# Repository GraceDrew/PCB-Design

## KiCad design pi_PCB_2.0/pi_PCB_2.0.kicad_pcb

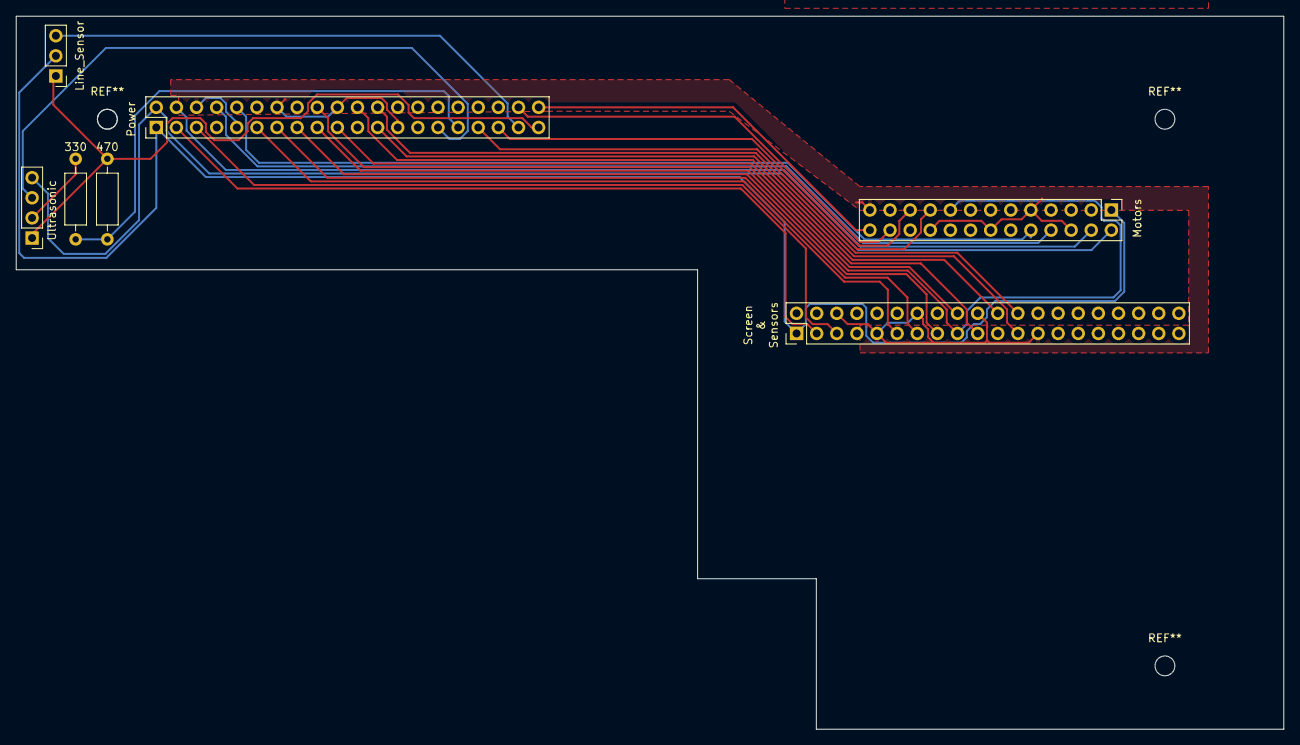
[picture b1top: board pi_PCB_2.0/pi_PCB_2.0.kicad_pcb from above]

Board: 2 copper layers, 160.0 x 90.0 mm, 7 parts (0 on the bottom side), 26 nets.

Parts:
330, 470: R_Small; R_Axial_DIN0207_L6.3mm_D2.5mm_P10.16mm_Horizontal
Line_Sensor: Conn_01x03_Socket; PinHeader_1x03_P2.54mm_Vertical
Motors: Conn_02x13_Odd_Even; PinHeader_2x13_P2.54mm_Vertical
Raspberry_Pi1: Power; PinHeader_2x20_P2.54mm_Vertical
Screen_and_Sensor_Header1: Screen_and_Sensor; PinHeader_2x20_P2.54mm_Vertical
Ultrasonic: Conn_01x04_Socket; PinHeader_1x04_P2.54mm_Vertical

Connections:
unnamed: 470.2, Line_Sensor.1 (Ground), Raspberry_Pi1.39 (GND), Ultrasonic.1 (GND)
unnamed: Line_Sensor.3 (Out), Raspberry_Pi1.37 (GPIO26)
unnamed: Line_Sensor.2 (VCC), Motors.1 (3V3_Power), Raspberry_Pi1.1 (3V3), Screen_and_Sensor_Header1.1 (3.3V_Power)
unnamed: Motors.17 (3V3_Power), Raspberry_Pi1.17 (3V3), Screen_and_Sensor_Header1.17 (3.3V_Power)
unnamed: Motors.4 (5V_Power), Raspberry_Pi1.4 (5V)
unnamed: Motors.19 (GPIO_13), Raspberry_Pi1.33 (PWM1/GPIO13)
unnamed: Motors.8 (GPIO_14), Raspberry_Pi1.8 (GPIO14/TXD)
unnamed: Motors.10 (GPIO_15), Raspberry_Pi1.10 (GPIO15/RXD)
unnamed: Motors.21 (GPIO_19), Raspberry_Pi1.35 (GPIO19/MISO1)
unnamed: Motors.24 (GPIO_20), Raspberry_Pi1.38 (GPIO20/MOSI1)
unnamed: Motors.26 (GPIO_21), Raspberry_Pi1.40 (GPIO21/SCLK1)
unnamed: Motors.6 (Ground), Motors.9 (Ground), Motors.14 (Ground), Motors.20 (Ground), Motors.25 (Ground), Raspberry_Pi1.6 (GND), Raspberry_Pi1.9 (GND), Raspberry_Pi1.14 (GND), Raspberry_Pi1.20 (GND), Raspberry_Pi1.25 (GND), Screen_and_Sensor_Header1.6 (Ground), Screen_and_Sensor_Header1.9 (Ground), Screen_and_Sensor_Header1.14 (Ground), Screen_and_Sensor_Header1.20 (Ground), Screen_and_Sensor_Header1.25 (Ground)
unnamed: Raspberry_Pi1.29 (GCLK1/GPIO5), Ultrasonic.3 (Trig)
unnamed: 330.1, 470.1, Raspberry_Pi1.31 (GCLK2/GPIO6)
unnamed: Raspberry_Pi1.11 (GPIO17), Screen_and_Sensor_Header1.11 (Ext_Reset)
unnamed: Raspberry_Pi1.15 (GPIO22), Screen_and_Sensor_Header1.15 (Touch_rst)
unnamed: Raspberry_Pi1.18 (GPIO24), Screen_and_Sensor_Header1.18 (Busy_out)
unnamed: Raspberry_Pi1.22 (GPIO25), Screen_and_Sensor_Header1.22 (Data_ctrl)
unnamed: Raspberry_Pi1.13 (GPIO27), Screen_and_Sensor_Header1.13 (Touch_iterp)
unnamed: Raspberry_Pi1.19 (MOSI0/GPIO10), Screen_and_Sensor_Header1.19 (SPI_MOSI)
unnamed: Raspberry_Pi1.23 (SCLK0/GPIO11), Screen_and_Sensor_Header1.23 (SPI_SCLK)
unnamed: Raspberry_Pi1.5 (SCL/GPIO3), Screen_and_Sensor_Header1.5 (Touch_Clk)
unnamed: Raspberry_Pi1.3 (SDA/GPIO2), Screen_and_Sensor_Header1.3 (Touch_Data)
unnamed: Raspberry_Pi1.24 (~CE0/GPIO8), Screen_and_Sensor_Header1.24 (SPI_select)
unnamed: 330.2, Ultrasonic.2 (Echo)
unnamed: Motors.2 (5V_Power), Raspberry_Pi1.2 (5V), Ultrasonic.4 (VCC)

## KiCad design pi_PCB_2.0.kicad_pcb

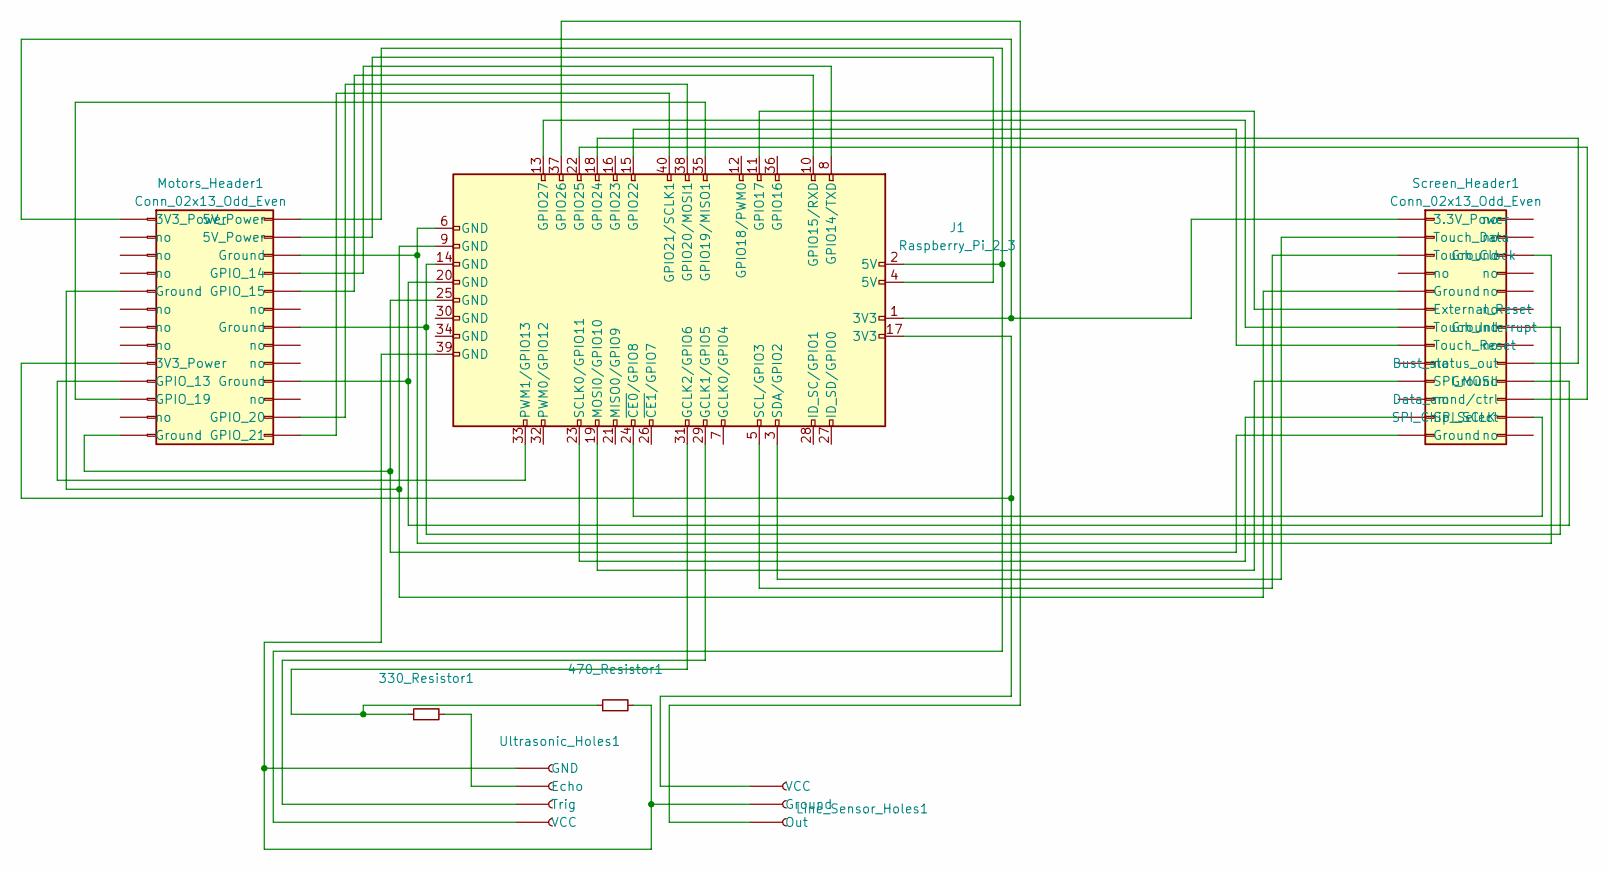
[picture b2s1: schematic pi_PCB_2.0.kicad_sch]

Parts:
330_Resistor1, 470_Resistor1: R_Small; R_Axial_DIN0204_L3.6mm_D1.6mm_P1.90mm_Vertical
J1: Raspberry_Pi_2_3; PinHeader_2x20_P2.54mm_Vertical
Line_Sensor_Holes1: Conn_01x03_Socket; PinHeader_1x03_P2.54mm_Vertical
Motors_Header1: Conn_02x13_Odd_Even; PinHeader_2x13_P2.54mm_Vertical
Screen_Header1: Conn_02x13_Odd_Even; PinHeader_2x13_P2.54mm_Vertical
Ultrasonic_Holes1: Conn_01x04_Socket; PinHeader_1x04_P2.54mm_Vertical

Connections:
unnamed: J1.4 (5V), Motors_Header1.4 (5V_Power)
unnamed: J1.29 (GCLK1/GPIO5), Ultrasonic_Holes1.3 (Trig)
unnamed: 330_Resistor1.1, 470_Resistor1.1, J1.31 (GCLK2/GPIO6)
unnamed: J1.6 (GND), Motors_Header1.6 (Ground), Screen_Header1.6 (Ground)
unnamed: J1.9 (GND), Motors_Header1.9 (Ground), Screen_Header1.9 (Ground)
unnamed: J1.14 (GND), Motors_Header1.14 (Ground), Screen_Header1.14 (Ground)
unnamed: J1.20 (GND), Motors_Header1.20 (Ground), Screen_Header1.20 (Ground)
unnamed: J1.25 (GND), Motors_Header1.25 (Ground), Screen_Header1.25 (Ground)
unnamed: J1.8 (GPIO14/TXD), Motors_Header1.8 (GPIO_14)
unnamed: J1.10 (GPIO15/RXD), Motors_Header1.10 (GPIO_15)
unnamed: J1.11 (GPIO17), Screen_Header1.11 (External_Reset)
unnamed: J1.35 (GPIO19/MISO1), Motors_Header1.21 (GPIO_19)
unnamed: J1.38 (GPIO20/MOSI1), Motors_Header1.24 (GPIO_20)
unnamed: J1.40 (GPIO21/SCLK1), Motors_Header1.26 (GPIO_21)
unnamed: J1.15 (GPIO22), Screen_Header1.15 (Touch_Reset)
unnamed: J1.18 (GPIO24), Screen_Header1.18 (Bust_status_out)
unnamed: J1.22 (GPIO25), Screen_Header1.22 (Data_cmnd/ctrl)
unnamed: J1.37 (GPIO26), Line_Sensor_Holes1.3 (Out)
unnamed: J1.13 (GPIO27), Screen_Header1.13 (Touch_Interrupt)
unnamed: J1.19 (MOSI0/GPIO10), Screen_Header1.19 (SPI_MOSI)
unnamed: J1.33 (PWM1/GPIO13), Motors_Header1.19 (GPIO_13)
unnamed: J1.23 (SCLK0/GPIO11), Screen_Header1.23 (SPI_SCLK)
unnamed: J1.5 (SCL/GPIO3), Screen_Header1.5 (Touch_Clock)
unnamed: J1.3 (SDA/GPIO2), Screen_Header1.3 (Touch_Data)
unnamed: J1.24 (~CE0/GPIO8), Screen_Header1.24 (SPI_Chip_Select)
unnamed: 470_Resistor1.2, J1.39 (GND), Line_Sensor_Holes1.2 (Ground), Ultrasonic_Holes1.1 (GND)
unnamed: J1.17 (3V3), Line_Sensor_Holes1.1 (VCC), Motors_Header1.17 (3V3_Power)
unnamed: J1.1 (3V3), Motors_Header1.1 (3V3_Power), Screen_Header1.1 (3.3V_Power)
unnamed: 330_Resistor1.2, Ultrasonic_Holes1.2 (Echo)
unnamed: J1.2 (5V), Motors_Header1.2 (5V_Power), Ultrasonic_Holes1.4 (VCC)

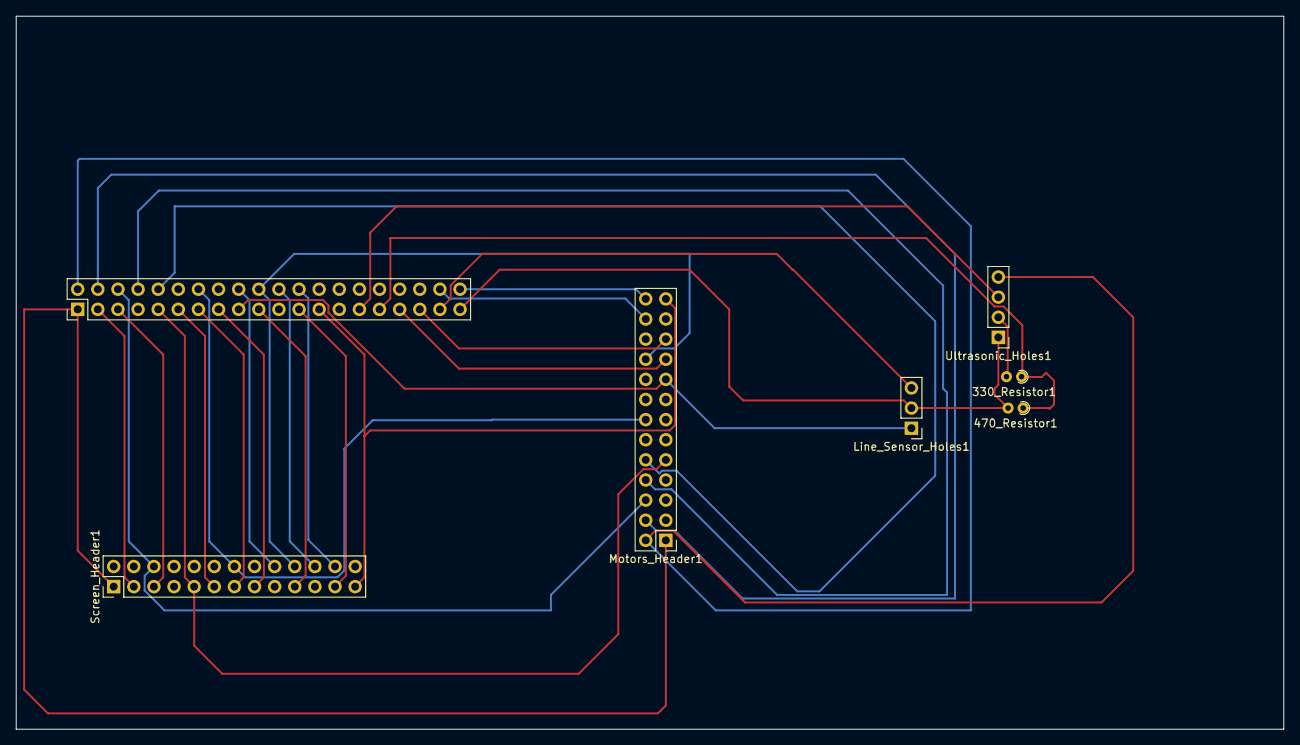
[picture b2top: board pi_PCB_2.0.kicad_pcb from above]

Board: 2 copper layers, 160.0 x 90.0 mm, 7 parts (0 on the bottom side), 30 nets.

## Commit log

2023-03-02 PCB Files
    PCB Files
2023-03-07 PCB Design 2.0
2023-03-07 PCB Final?
2023-03-07 Final 2
2023-03-08 Final 3
